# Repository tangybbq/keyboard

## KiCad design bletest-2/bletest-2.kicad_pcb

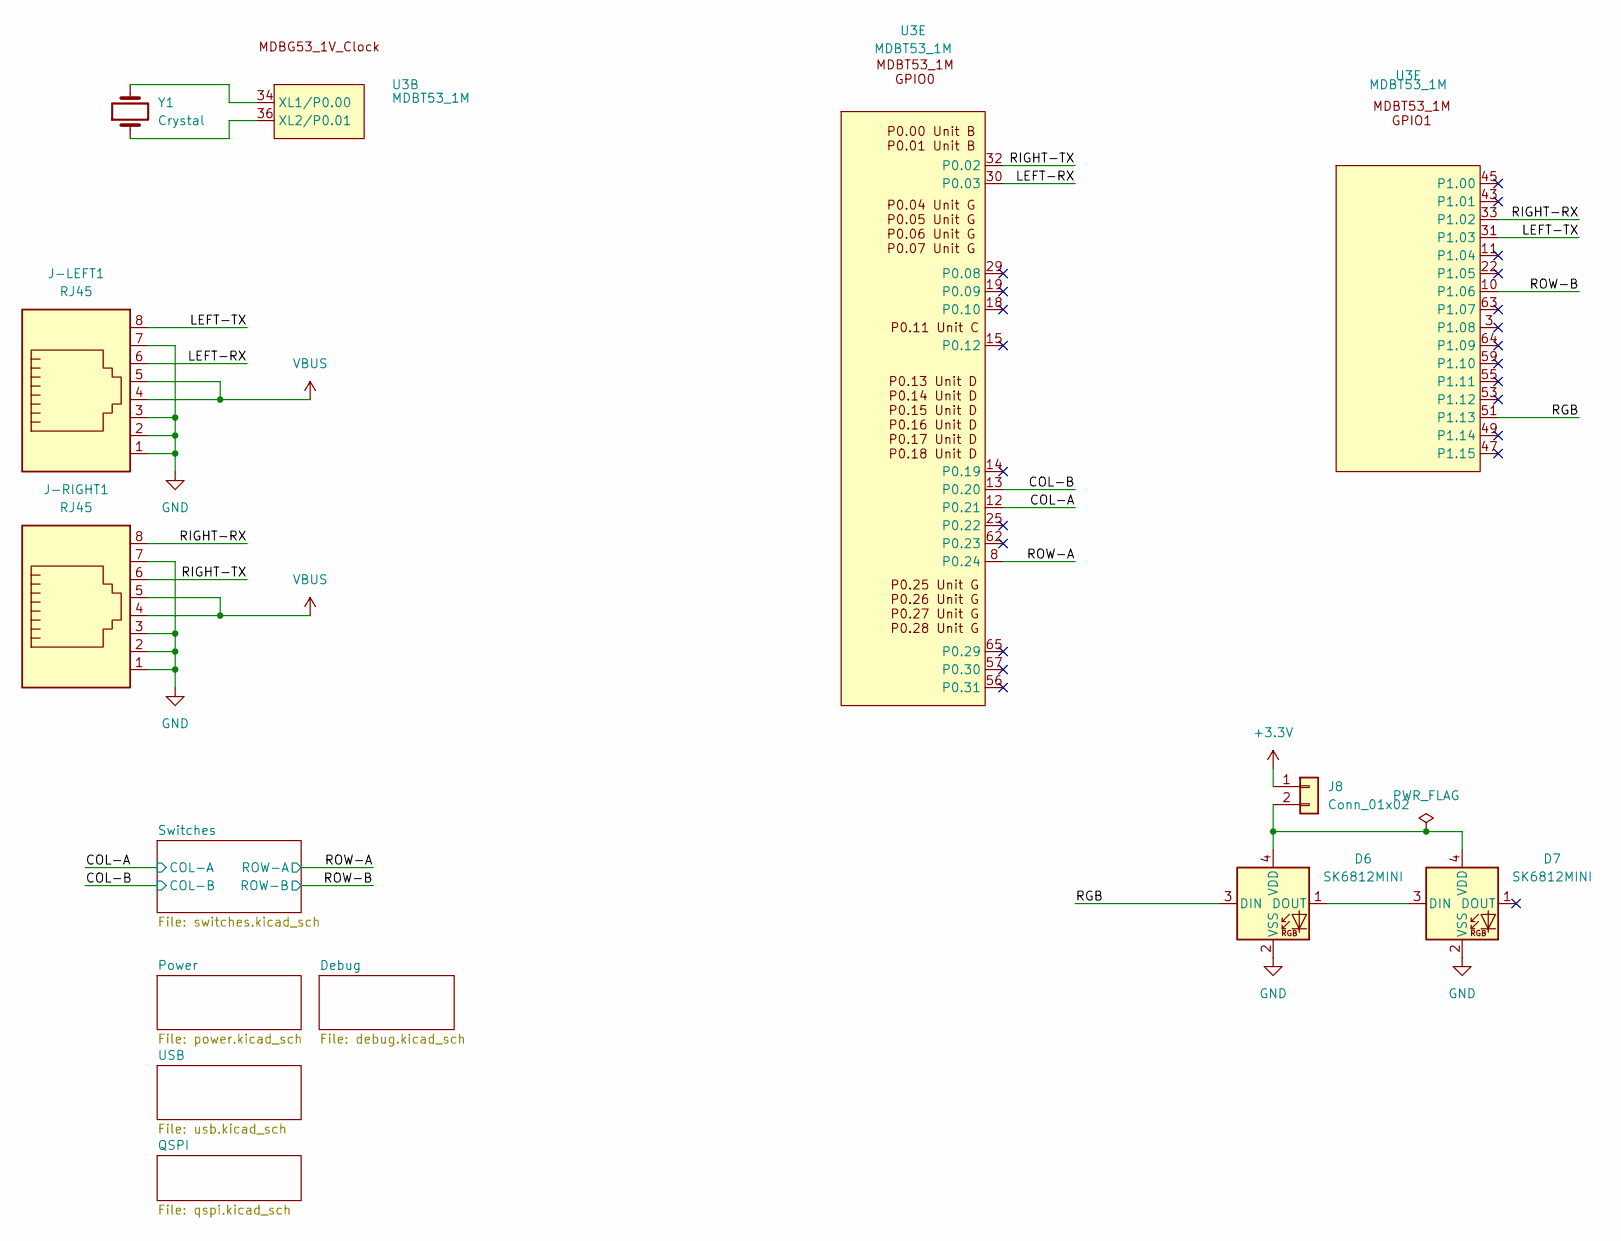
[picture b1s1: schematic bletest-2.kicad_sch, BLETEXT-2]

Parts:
D6, D7: SK6812MINI; LED_SK6812MINI_PLCC4_3.5x3.5mm_P1.75mm
J8: Conn_01x02; PinHeader_1x02_P2.54mm_Vertical
J-LEFT1: RJ45; RJ45_Amphenol_54602-x08_Horizontal
J-RIGHT1: RJ45; RJ45_Amphenol_54602-x08_Horizontal
U3: MDBT53_1M
Y1: Crystal; Crystal_SMD_3215-2Pin_3.2x1.5mm

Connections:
+3.3V: J8.1; also elsewhere on the board
/COL-A: U3.12 (P0.21); also elsewhere on the board
/COL-B: U3.13 (P0.20); also elsewhere on the board
/LEFT-RX: J-LEFT1.6, U3.30 (P0.03)
/LEFT-TX: J-LEFT1.8, U3.31 (P1.03)
/RGB: D6.3 (DIN), U3.51 (P1.13)
/RIGHT-RX: J-RIGHT1.8, U3.33 (P1.02)
/RIGHT-TX: J-RIGHT1.6, U3.32 (P0.02)
/ROW-A: U3.8 (P0.24); also elsewhere on the board
/ROW-B: U3.10 (P1.06); also elsewhere on the board
GND: D6.2 (VSS), D7.2 (VSS), J-LEFT1.1, J-LEFT1.2, J-LEFT1.3, J-LEFT1.7, J-RIGHT1.1, J-RIGHT1.2, J-RIGHT1.3, J-RIGHT1.7; also elsewhere on the board
unnamed: D6.1 (DOUT), D7.3 (DIN)
unnamed: D6.4 (VDD), D7.4 (VDD), J8.2
unnamed: U3.34 (XL1/P0.00), Y1.2
unnamed: U3.36 (XL2/P0.01), Y1.1
VBUS: J-LEFT1.4, J-LEFT1.5, J-RIGHT1.4, J-RIGHT1.5; also elsewhere on the board

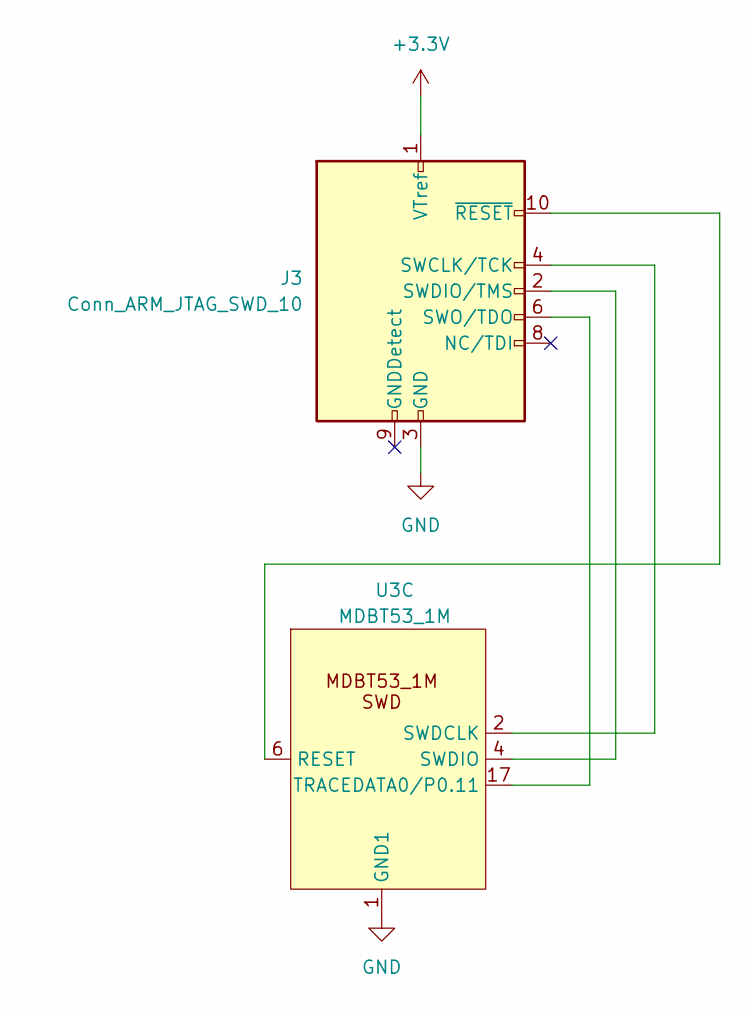
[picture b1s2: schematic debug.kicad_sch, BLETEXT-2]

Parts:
J3: Conn_ARM_JTAG_SWD_10; Cortex-M-Debug10
U3: MDBT53_1M

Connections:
+3.3V: J3.1 (VTref); also elsewhere on the board
GND: J3.3 (GND), J3.5 (GND), U3.1 (GND1); also elsewhere on the board
unnamed: J3.4 (SWCLK/TCK), U3.2 (SWDCLK)
unnamed: J3.2 (SWDIO/TMS), U3.4 (SWDIO)
unnamed: J3.6 (SWO/TDO), U3.17 (TRACEDATA0/P0.11)
unnamed: J3.10 (~RESET), U3.6 (RESET)

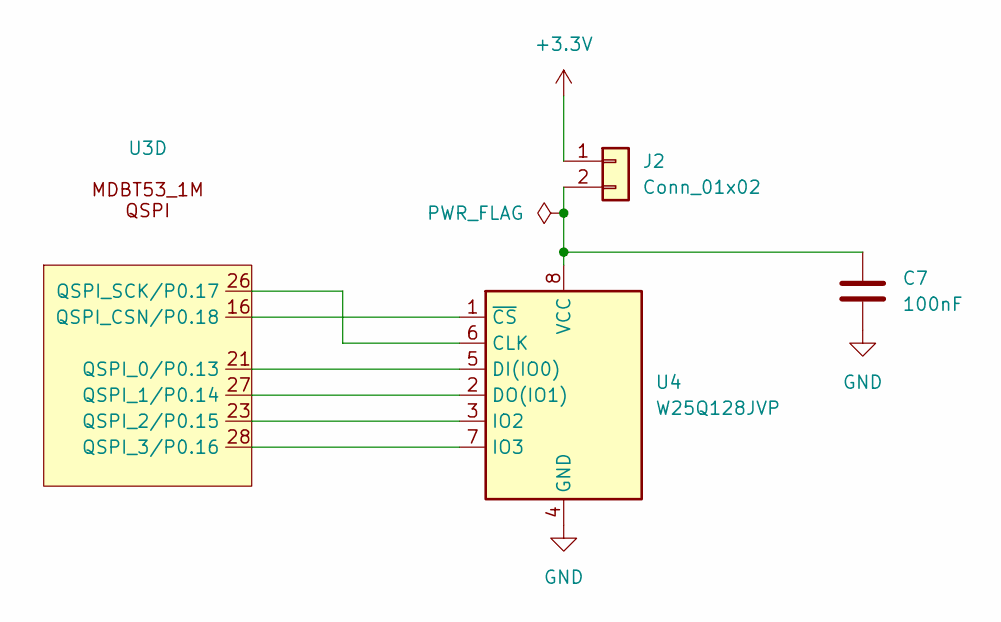
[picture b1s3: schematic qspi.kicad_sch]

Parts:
C7: 100nF; C_0603_1608Metric
J2: Conn_01x02; PinHeader_1x02_P2.54mm_Vertical
U3: MDBT53_1M
U4: W25Q128JVP; WSON-8-1EP_6x5mm_P1.27mm_EP3.4x4.3mm

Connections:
+3.3V: J2.1; also elsewhere on the board
GND: C7.2, U4.4 (GND); also elsewhere on the board
unnamed: C7.1, J2.2, U4.8 (VCC)
unnamed: U3.21 (QSPI_0/P0.13), U4.5 (DI(IO0))
unnamed: U3.27 (QSPI_1/P0.14), U4.2 (DO(IO1))
unnamed: U3.23 (QSPI_2/P0.15), U4.3 (IO2)
unnamed: U3.28 (QSPI_3/P0.16), U4.7 (IO3)
unnamed: U3.16 (QSPI_CSN/P0.18), U4.1 (~CS)
unnamed: U3.26 (QSPI_SCK/P0.17), U4.6 (CLK)

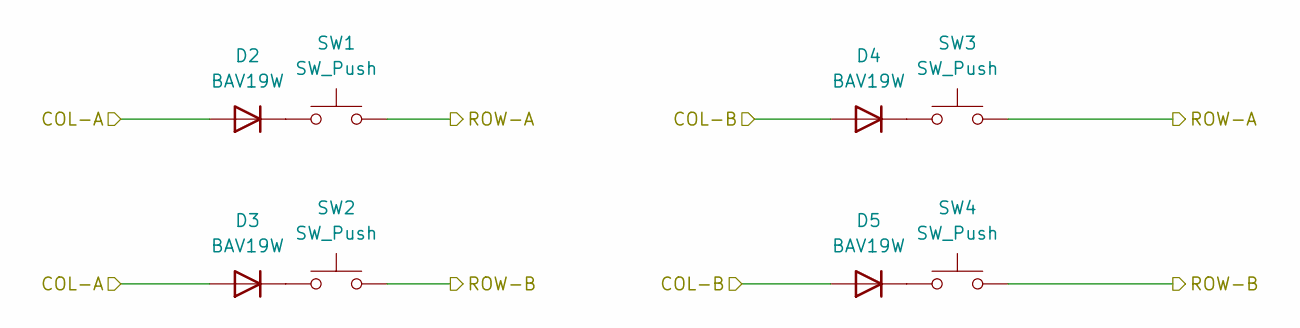
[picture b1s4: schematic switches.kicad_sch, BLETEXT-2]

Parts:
D2, D3, D4, D5: BAV19W; Nexperia_CFP3_SOD-123W
SW1, SW2, SW3, SW4: SW_Push; Kailh_socket_PG1350

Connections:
/COL-A: D2.2 (A), D3.2 (A); also elsewhere on the board
/COL-B: D4.2 (A), D5.2 (A); also elsewhere on the board
/ROW-A: SW1.2, SW3.2; also elsewhere on the board
/ROW-B: SW2.2, SW4.2; also elsewhere on the board
unnamed: D2.1 (K), SW1.1
unnamed: D3.1 (K), SW2.1
unnamed: D4.1 (K), SW3.1
unnamed: D5.1 (K), SW4.1

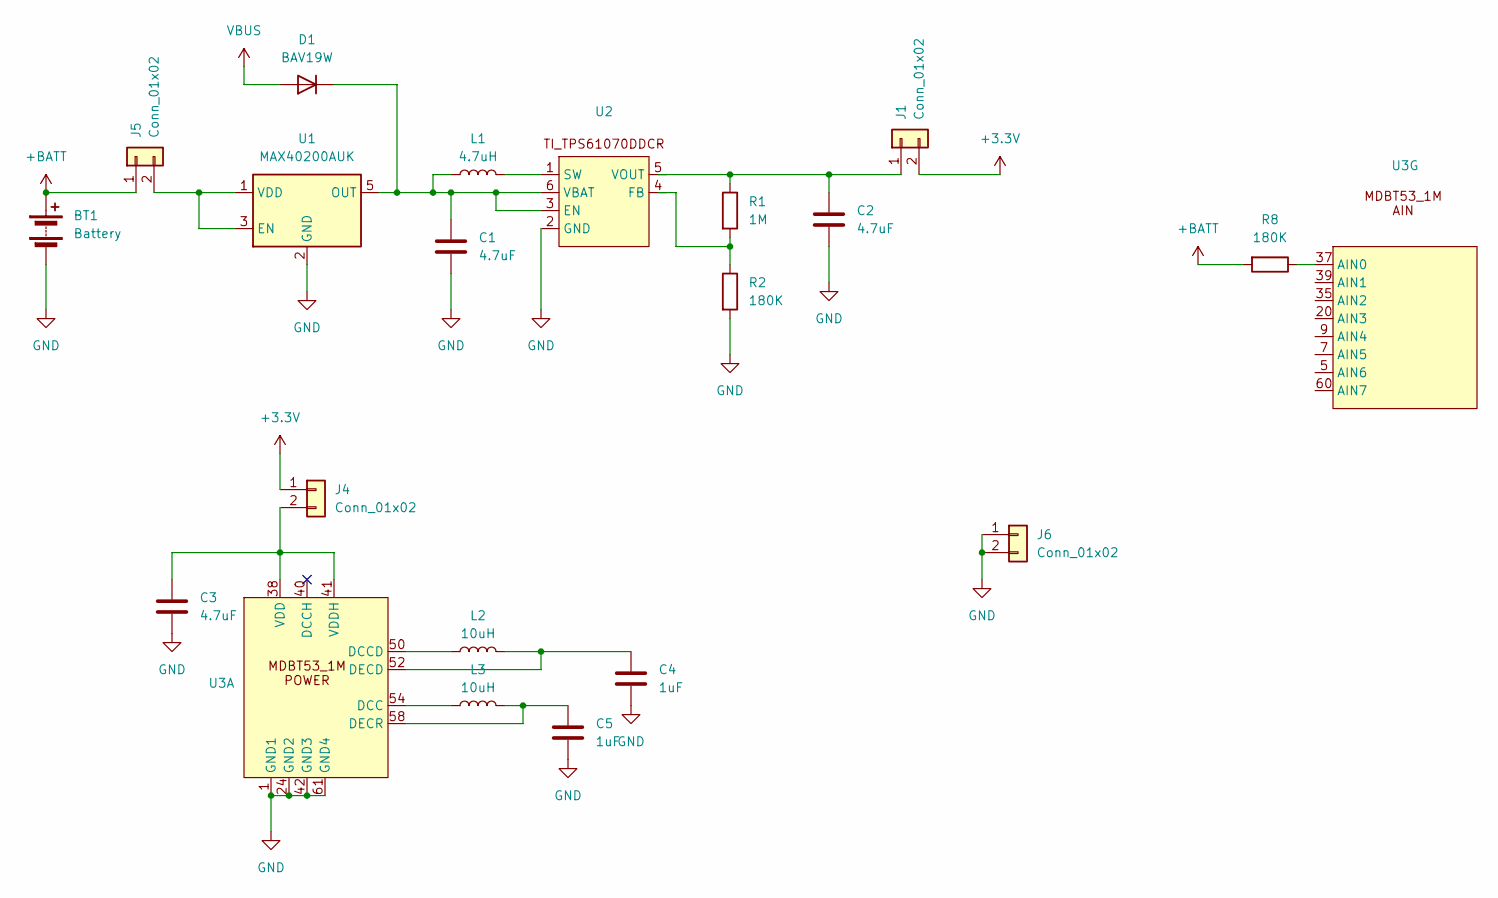
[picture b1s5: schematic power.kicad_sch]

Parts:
BT1: Battery; BAT-2xAA-SHELL-CASE-BOX-NOSCREW
C1, C2, C3: 4.7uF; C_0603_1608Metric
C4, C5: 1uF; C_0603_1608Metric
D1: BAV19W; Nexperia_CFP3_SOD-123W
J1, J4, J5, J6: Conn_01x02; PinHeader_1x02_P2.54mm_Vertical
L1: 4.7uH; L_0805_2012Metric
L2, L3: 10uH; L_0805_2012Metric
R1: 1M; R_0603_1608Metric
R2, R8: 180K; R_0603_1608Metric
U1: MAX40200AUK; SOT-23-5
U2: SOT-23-6
U3: MDBT53_1M

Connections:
+3.3V: J1.2, J4.1; also elsewhere on the board
+BATT: BT1.1 (+), J5.1, R8.2
GND: BT1.2 (-), C1.2, C2.2, C3.2, C4.2, C5.2, J6.1, J6.2, R2.2, U1.2 (GND), U2.2 (GND), U3.1 (GND1), U3.24 (GND2), U3.42 (GND3), U3.61 (GND4); also elsewhere on the board
unnamed: C1.1, D1.1 (K), L1.1, U1.5 (OUT), U2.3 (EN), U2.6 (VBAT)
unnamed: C3.1, J4.2, U3.38 (VDD), U3.41 (VDDH)
unnamed: J5.2, U1.1 (VDD), U1.3 (EN)
unnamed: L1.2, U2.1 (SW)
unnamed: L3.1, U3.54 (DCC)
unnamed: L2.1, U3.50 (DCCD)
unnamed: C4.1, L2.2, U3.52 (DECD)
unnamed: C5.1, L3.2, U3.58 (DECR)
unnamed: R8.1, U3.37 (AIN0/P0.04)
VBUS: D1.2 (A); also elsewhere on the board

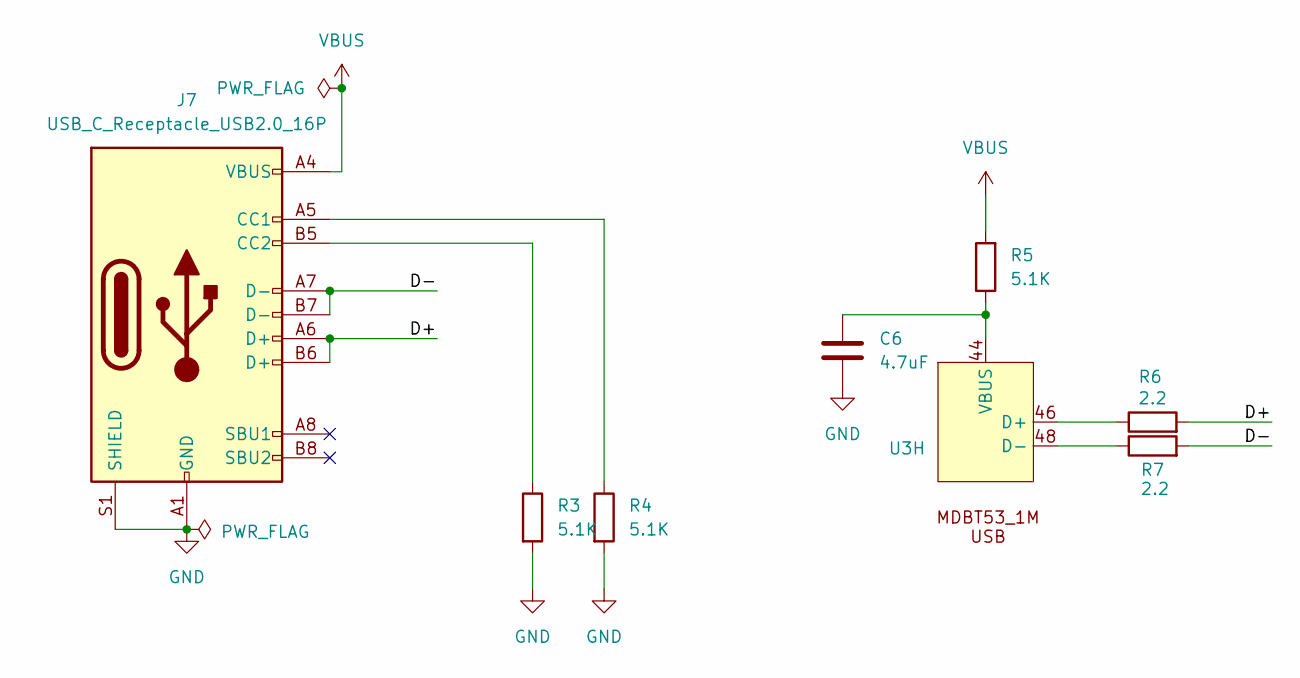
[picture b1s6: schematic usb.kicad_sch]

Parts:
C6: 4.7uF; C_0603_1608Metric
J7: USB_C_Receptacle_USB2.0_16P; USB_C_Receptacle_GCT_USB4085
R3, R4, R5: 5.1K; R_0603_1608Metric
R6, R7: 2.2; R_0603_1608Metric
U3: MDBT53_1M

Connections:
/USB/D+: J7.A6 (D+), J7.B6 (D+), R6.2
/USB/D-: J7.A7 (D-), J7.B7 (D-), R7.2
GND: C6.2, J7.A1 (GND), J7.A12 (GND), J7.B1 (GND), J7.B12 (GND), J7.S1 (SHIELD), R3.2, R4.2; also elsewhere on the board
unnamed: J7.A5 (CC1), R4.1
unnamed: J7.B5 (CC2), R3.1
unnamed: R6.1, U3.46 (D+)
unnamed: R7.1, U3.48 (D-)
unnamed: C6.1, R5.1, U3.44 (VBUS)
VBUS: J7.A4 (VBUS), J7.A9 (VBUS), J7.B4 (VBUS), J7.B9 (VBUS), R5.2; also elsewhere on the board

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
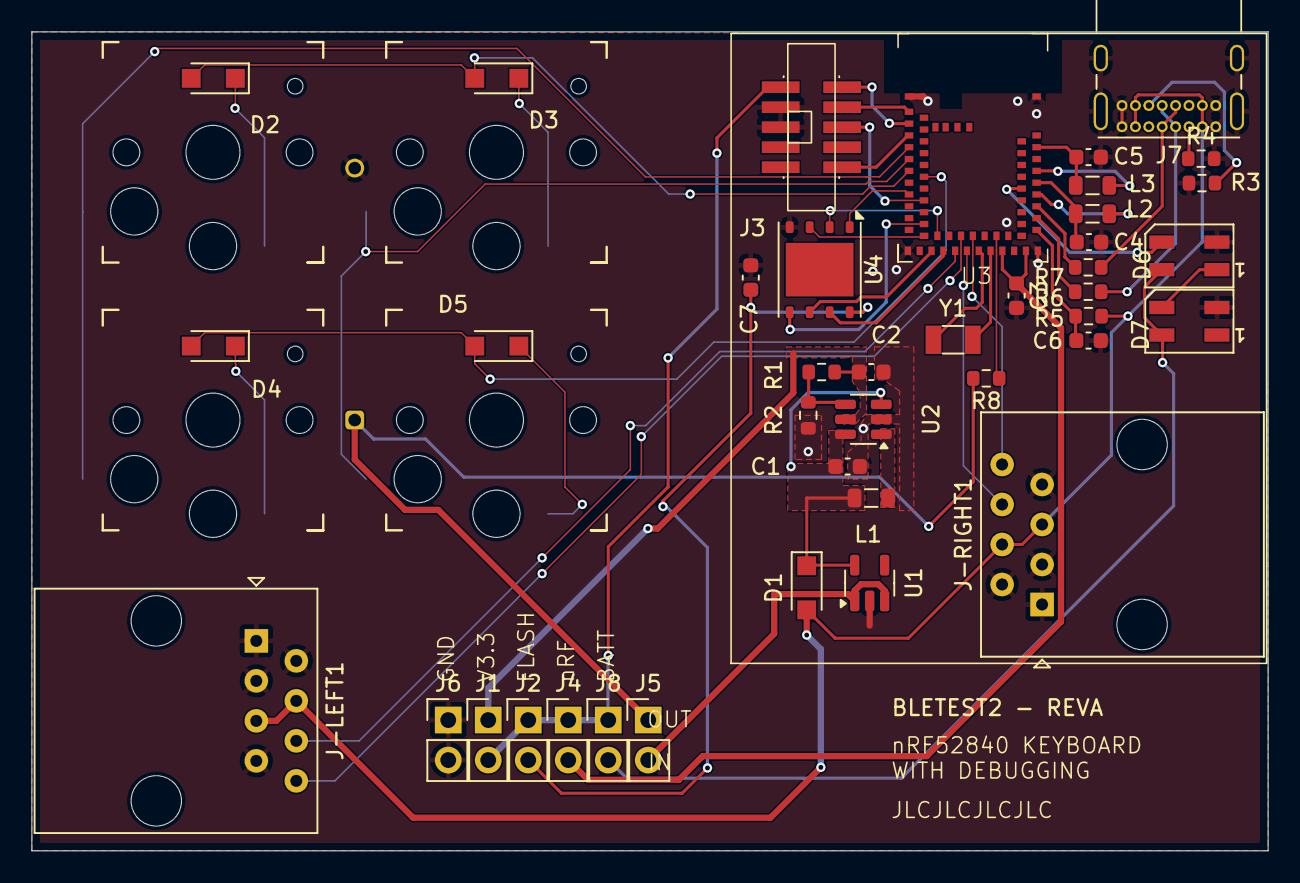
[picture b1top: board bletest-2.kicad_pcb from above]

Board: 2 copper layers, 78.5 x 52.0 mm, 45 parts (1 on the bottom side), 50 nets.

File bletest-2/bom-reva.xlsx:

Reference | Value | Qty | Datasheet | Footprint | DNP
BT1 | Battery | 1 | ~ | davidb-keyboard-foot:BAT-2xAA-SHELL-CASE-BOX-NOSCREW
C1,C2,C3,C6 | 4.7uF | 4 | ~ | Capacitor_SMD:C_0603_1608Metric
C4,C5 | 1uF | 2 | ~ | Capacitor_SMD:C_0603_1608Metric
C7 | 100nF | 1 | ~ | Capacitor_SMD:C_0603_1608Metric
D1,D2,D3,D4,D5 | BAV19W | 5 | ~ | Diode_SMD:Nexperia_CFP3_SOD-123W
D6,D7 | SK6812MINI | 2 | https://cdn-shop.adafruit.com/product-files/2686/SK6812MINI_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 | LED_SMD:LED_SK6812MINI_PLCC4_3.5x3.5mm_P1.75mm
J-LEFT1,J-RIGHT1 | RJ45 | 2 | ~ | Connector_RJ:RJ45_Amphenol_54602-x08_Horizontal
J1,J2,J4,J5,J6,J8 | Conn_01x02 | 6 | ~ | Connector_PinHeader_2.54mm:PinHeader_1x02_P2.54mm_Vertical
J3 | Conn_ARM_JTAG_SWD_10 | 1 | http://infocenter.arm.com/help/topic/com.arm.doc.ddi0314h/DD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 | davidb-keyboard-foot:Cortex-M-Debug10
J7 | USB_C_Receptacle_USB2.0_16P | 1 | https://www.usb.org/sites/default/files/documents/usb_type-c.zip | Connector_USB:USB_C_Receptacle_GCT_USB4085
L1 | 4.7uH | 1 | ~ | Inductor_SMD:L_0805_2012Metric
L2,L3 | 10uH | 2 | ~ | Inductor_SMD:L_0805_2012Metric
R1 | 1M | 1 | ~ | Resistor_SMD:R_0603_1608Metric
R2,R8 | 180K | 2 | ~ | Resistor_SMD:R_0603_1608Metric
R3,R4,R5 | 5.1K | 3 | ~ | Resistor_SMD:R_0603_1608Metric
R6,R7 | 2.2000000000000002 | 2 | ~ | Resistor_SMD:R_0603_1608Metric
SW1,SW2,SW3,SW4 | SW_Push | 4 | ~ | Keyboard Switches:Kailh_socket_PG1350
U1 | MAX40200AUK | 1 | https://datasheets.maximintegrated.com/en/ds/MAX40200.pdf | Package_TO_SOT_SMD:SOT-23-5
U2,U3 | ~ | 2 |  | -- mixed values --
U4 | W25Q128JVP | 1 | https://www.winbond.com/resource-files/w25q128jv_dtr%20revc%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 | Package_SON:WSON-8-1EP_6x5mm_P1.27mm_EP3.4x4.3mm
Y1 | Crystal | 1 | ~ | Crystal:Crystal_SMD_3215-2Pin_3.2x1.5mm

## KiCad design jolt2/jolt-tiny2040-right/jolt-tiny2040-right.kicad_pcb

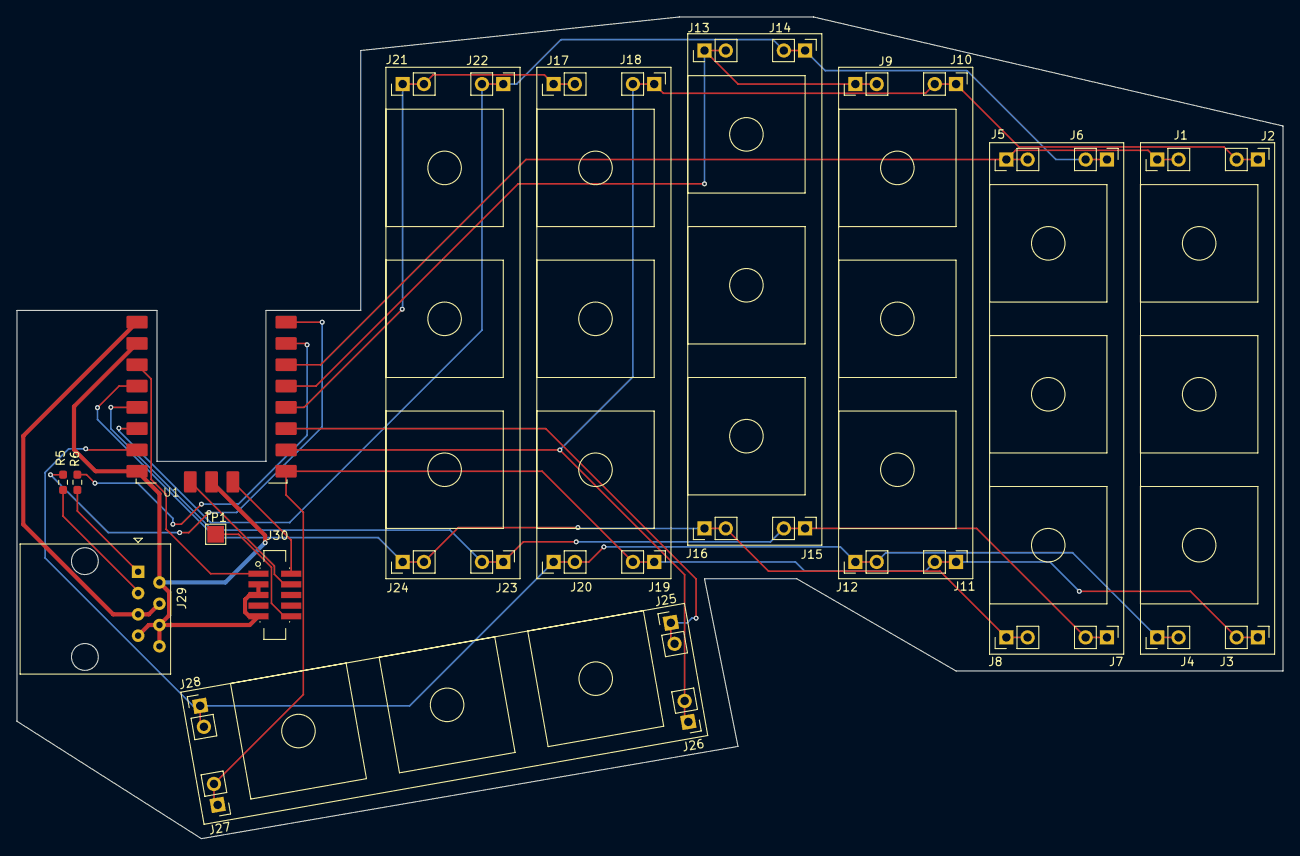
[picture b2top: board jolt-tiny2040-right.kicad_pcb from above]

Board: 2 copper layers, 151.0 x 98.0 mm, 34 parts (0 on the bottom side), 20 nets.

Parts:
J1, J2, J3, J4, J5, J6, J7, J8, J9, J10, J11, J12, J13, J14, J15, J16, J17, J18, J19, J20, J21, J22, J23, J24, J25, J26, J27, J28: Conn_01x02_Pin; PinHeader_1x02_P2.54mm_Vertical
J29: RJ45; RJ45_Amphenol_54602-x08_Horizontal
J30: Conn_ARM_JTAG_SWD_10; Cortex-M-Debug10
R5, R6: 27; R_0603_1608Metric_Pad0.98x0.95mm_HandSolder
TP1: Reset; TestPoint_Pad_2.0x2.0mm
U1: Pimoroni-Tiny2040

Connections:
+3.3V: J30.1 (VTref), U1.3V
/COL-A: J1.1, J1.2, J5.1, J5.2, U1.2
/COL-B: J9.1, J9.2, J13.1, J13.2, U1.3
/COL-C: J17.1, J17.2, J21.1, J21.2, U1.4
/COL-D: J25.1, J25.2, U1.5
/ROW-A: J2.1, J2.2, J10.1, J10.2, J18.1, J18.2, J26.1, J26.2, U1.6
/ROW-B: J3.1, J3.2, J11.1, J11.2, J19.1, J19.2, J27.1, J27.2, U1.7
/ROW-C: J4.1, J4.2, J12.1, J12.2, J20.1, J20.2, J28.1, J28.2, U1.A0
/ROW-D: J6.1, J6.2, J14.1, J14.2, J22.1, J22.2, U1.A1
/ROW-E: J7.1, J7.2, J15.1, J15.2, J23.1, J23.2, U1.A2
/ROW-F: J8.1, J8.2, J16.1, J16.2, J24.1, J24.2, U1.A3
GND: J29.2, J29.6, J29.7, J29.8, J30.3 (GND), J30.5 (GND), J30.9 (GNDDetect), U1.GND1 (GND), U1.GND2 (GND), U1.GND3 (GND)
unnamed: R5.1, U1.0
unnamed: R6.1, U1.1
RUN: J30.10 (~RESET), TP1.1
SERRX: J29.1, R6.2
SERTX: J29.3, R5.2
SWCLK: J30.4 (SWCLK/TCK), U1.SWC
SWDIO: J30.2 (SWDIO/TMS), U1.SWD
VBUS: J29.4, J29.5, U1.5V

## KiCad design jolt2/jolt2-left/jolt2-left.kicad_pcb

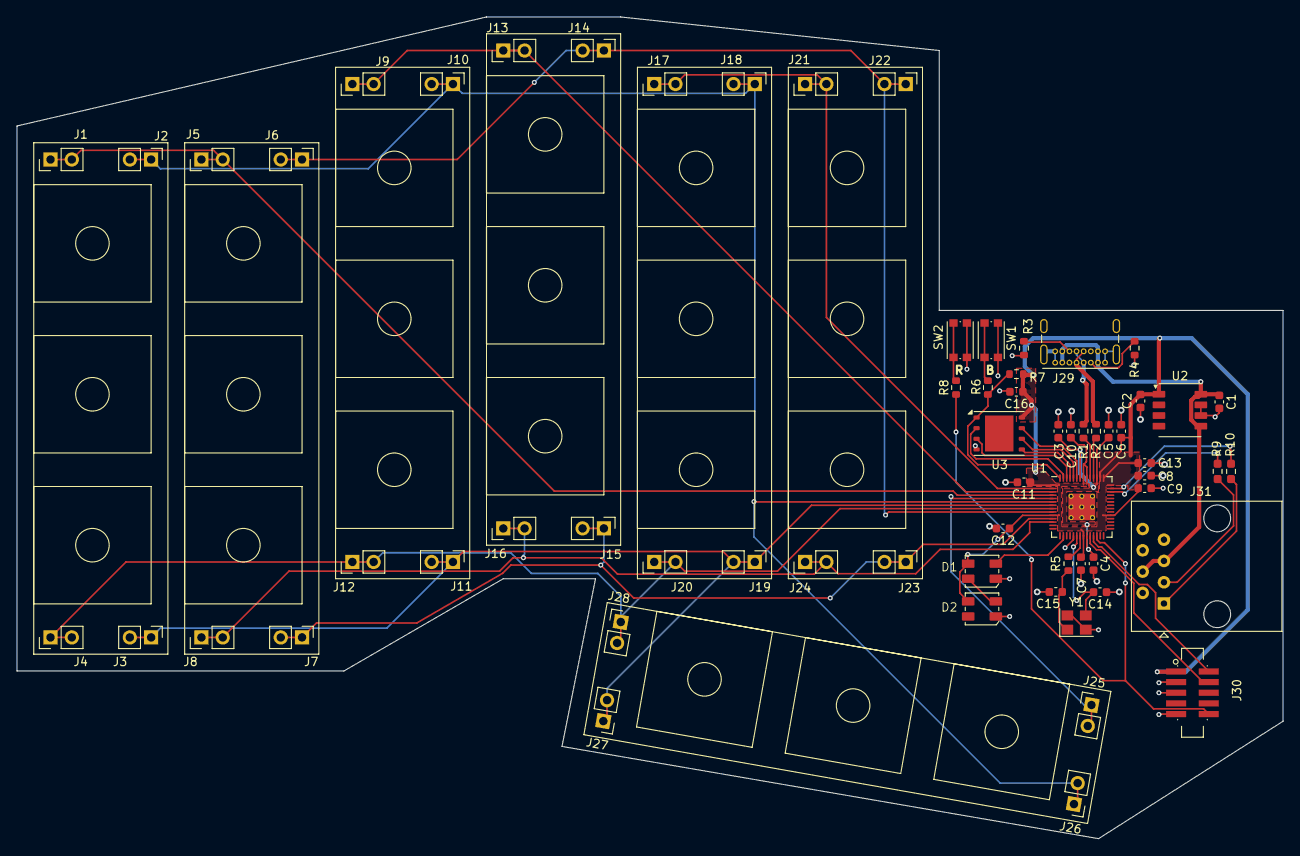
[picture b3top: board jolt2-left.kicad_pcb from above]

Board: 2 copper layers, 151.0 x 98.0 mm, 65 parts (0 on the bottom side), 40 nets.

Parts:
C1, C2: 10u; C_0603_1608Metric
C3, C4, C7, C8, C9, C10, C11, C12, C13, C16: 100n; C_0603_1608Metric
C5, C6: 1u; C_0603_1608Metric
C14, C15: 12p; C_0603_1608Metric
D1, D2: SK6812MINI-HS; SK6812-MINI-HS
J1, J2, J3, J4, J5, J6, J7, J8, J9, J10, J11, J12, J13, J14, J15, J16, J17, J18, J19, J20, J21, J22, J23, J24, J25, J26, J27, J28: Conn_01x02_Pin; PinHeader_1x02_P2.54mm_Vertical
J29: USB_C_Receptacle_USB2.0_14P; USB_C_Receptacle_GCT_USB4085
J30: Conn_ARM_JTAG_SWD_10; Cortex-M-Debug10
J31: RJ45; RJ45_Amphenol_54602-x08_Horizontal
R1, R2: 27; R_0603_1608Metric
R3, R4: 5.1k; R_0603_1608Metric
R5, R6, R8: 1k; R_0603_1608Metric
R7: 10k; R_0603_1608Metric
R9, R10: 27; R_0603_1608Metric_Pad0.98x0.95mm_HandSolder
SW1, SW2: SW_SPST; SW_Push_1P1T_NO_CK_KMR2
U1: RP2040; RP2040-QFN-56
U2: AP2112-M3.3; AP2112M-SO8
U3: W25Q128JVP; WSON-8-1EP_6x5mm_P1.27mm_EP3.4x4.3mm
Y1: ABM8-272-T3; Crystal_SMD_Abracon_ABM8G-4Pin_3.2x2.5mm

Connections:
+1V1: C3.1, C4.1, C5.1, U1.23 (DVDD), U1.45 (VREG_VOUT), U1.50 (DVDD)
+3.3V: C2.1, C6.1, C7.1, C8.1, C9.1, C10.1, C11.1, C12.1, C13.1, C16.1, D1.3 (VDD), D2.3 (VDD), J30.1 (VTref), R7.2, U1.1 (IOVDD), U1.10 (IOVDD), U1.22 (IOVDD), U1.33 (IOVDD), U1.42 (IOVDD), U1.43 (ADC_AVDD), U1.44 (VREG_IN), U1.48 (USB_VDD), U1.49 (IOVDD), U2.1 (VOUT), U3.8 (VCC)
/COL-A: J1.1, J1.2, J5.1, J5.2, U1.4 (GPIO2)
/COL-B: J9.1, J9.2, J13.1, J13.2, U1.3 (GPIO1)
/COL-C: J17.1, J17.2, J21.1, J21.2, U1.2 (GPIO0)
/COL-D: J25.1, J25.2, U1.5 (GPIO3)
/ROW-A: J2.1, J2.2, J10.1, J10.2, J18.1, J18.2, J26.1, J26.2, U1.6 (GPIO4)
/ROW-B: J3.1, J3.2, J11.1, J11.2, J19.1, J19.2, J27.1, J27.2, U1.7 (GPIO5)
/ROW-C: J4.1, J4.2, J12.1, J12.2, J20.1, J20.2, J28.1, J28.2, U1.8 (GPIO6)
/ROW-D: J6.1, J6.2, J14.1, J14.2, J22.1, J22.2, U1.9 (GPIO7)
/ROW-E: J7.1, J7.2, J15.1, J15.2, J23.1, J23.2, U1.11 (GPIO8)
/ROW-F: J8.1, J8.2, J16.1, J16.2, J24.1, J24.2, U1.12 (GPIO9)
/USB_D+: J29.A6 (D+), J29.B6 (D+), R1.2
/USB_D-: J29.A7 (D-), J29.B7 (D-), R2.2
GND: C1.2, C2.2, C3.2, C4.2, C5.2, C6.2, C7.2, C8.2, C9.2, C10.2, C11.2, C12.2, C13.2, C14.1, C15.1, C16.2, D1.1 (VSS), D2.1 (VSS), J29.A1 (GND), J29.A12 (GND), J29.B1 (GND), J29.B12 (GND), J29.S1 (SHIELD), J30.3 (GND), J30.5 (GND), J30.9 (GNDDetect), J31.2, J31.6, J31.7, J31.8, R3.2, R4.2, SW1.1 (A), SW2.1 (A), U1.19 (TESTEN), U1.57 (GND), U2.6 (GND), U2.7 (GND), U3.4 (GND), Y1.2, Y1.4
unnamed: C15.2, R5.1, Y1.1
unnamed: D1.4 (DOUT), D2.2 (DIN)
unnamed: J29.A5 (CC1), R4.1
unnamed: J29.B5 (CC2), R3.1
unnamed: J31.1, R10.1
unnamed: J31.3, R9.1
unnamed: R6.1, SW1.2 (B)
unnamed: R8.2, SW2.2 (B)
unnamed: R2.1, U1.46 (USB_DM)
unnamed: R1.1, U1.47 (USB_DP)
unnamed: C14.2, U1.20 (XIN), Y1.3
unnamed: R5.2, U1.21 (XOUT)
QSPI.SCLK: U1.52 (QSPI_SCLK), U3.6 (CLK)
QSPI.SD0: U1.53 (QSPI_SD0), U3.5 (DI(IO0))
QSPI.SD1: U1.55 (QSPI_SD1), U3.2 (DO(IO1))
QSPI.SD2: U1.54 (QSPI_SD2), U3.3 (IO2)
QSPI.SD3: U1.51 (QSPI_SD3), U3.7 (IO3)
QSPI.SS: R6.2, R7.1, U1.56 (QSPI_SS), U3.1 (~CS)
RGB: D1.2 (DIN), U1.16 (GPIO13)
RUN: J30.10 (~RESET), R8.1, U1.26 (RUN)
SERRX: R10.2, U1.41 (GPIO29_ADC3)
SERTX: R9.2, U1.40 (GPIO28_ADC2)
SWCLK: J30.4 (SWCLK/TCK), U1.24 (SWCLK)
SWDIO: J30.2 (SWDIO/TMS), U1.25 (SWD)
VBUS: C1.1, J29.A4 (VBUS), J29.A9 (VBUS), J29.B4 (VBUS), J29.B9 (VBUS), J31.4, J31.5, U2.5 (EN), U2.8 (VIN)

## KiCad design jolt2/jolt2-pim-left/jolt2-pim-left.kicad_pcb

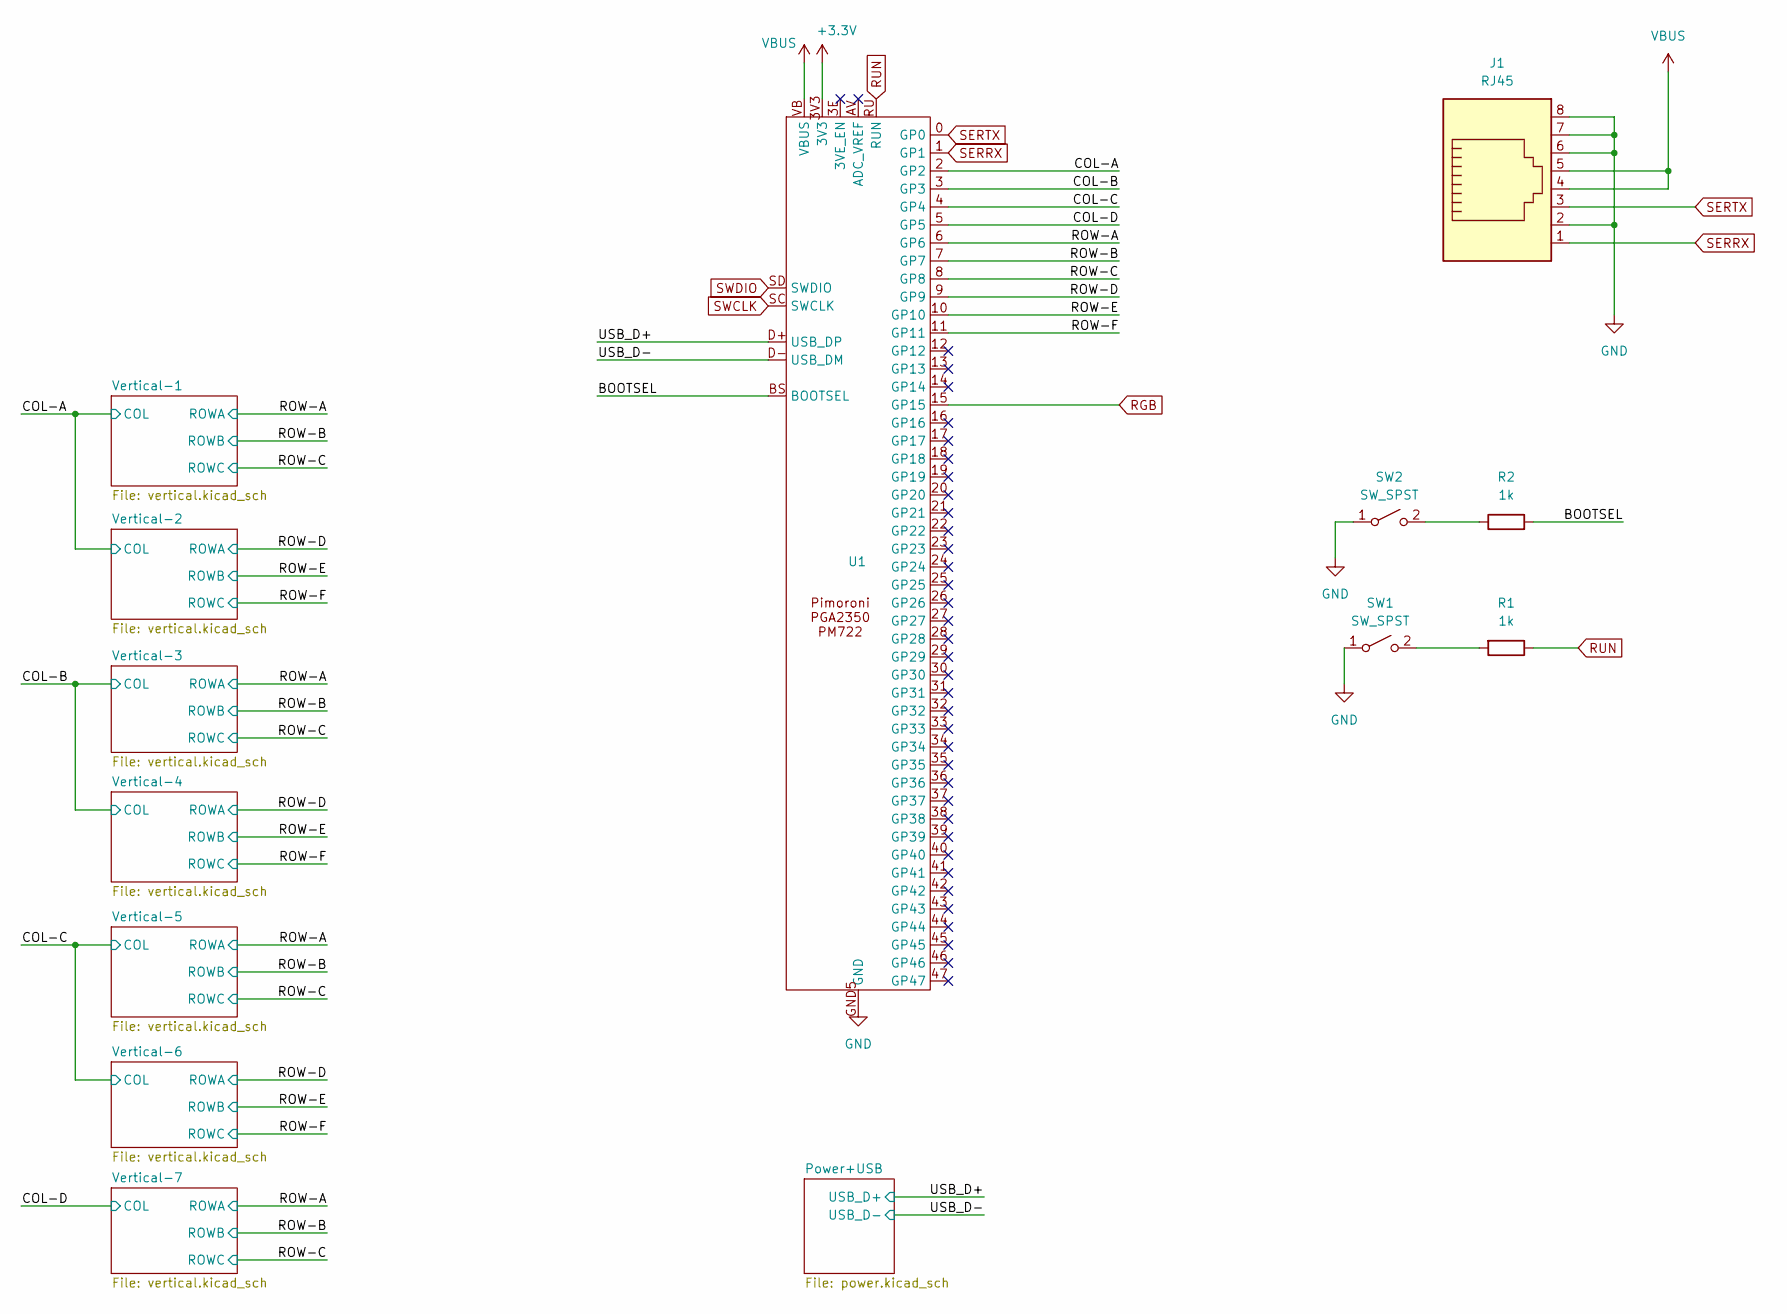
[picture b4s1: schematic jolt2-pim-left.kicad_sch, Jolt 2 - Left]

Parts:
J1: RJ45; RJ45_Amphenol_54602-x08_Horizontal
R1, R2: 1k; R_0603_1608Metric
SW1, SW2: SW_SPST; SW_Push_1P1T_NO_CK_KMR2
U1: PIMORONI-PGA2035-PM722

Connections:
+3.3V: U1.3V3; also elsewhere on the board
/BOOTSEL: R2.2, U1.BS (BOOTSEL)
/COL-A: U1.2 (GP2); also elsewhere on the board
/COL-B: U1.3 (GP3); also elsewhere on the board
/COL-C: U1.4 (GP4); also elsewhere on the board
/COL-D: U1.5 (GP5); also elsewhere on the board
/ROW-A: U1.6 (GP6); also elsewhere on the board
/ROW-B: U1.7 (GP7); also elsewhere on the board
/ROW-C: U1.8 (GP8); also elsewhere on the board
/ROW-D: U1.9 (GP9); also elsewhere on the board
/ROW-E: U1.10 (GP10); also elsewhere on the board
/ROW-F: U1.11 (GP11); also elsewhere on the board
/USB_D+: U1.D+ (USB_DP); also elsewhere on the board
/USB_D-: U1.D- (USB_DM); also elsewhere on the board
GND: J1.2, J1.6, J1.7, J1.8, SW1.1 (A), SW2.1 (A), U1.GND1 (GND), U1.GND2 (GND), U1.GND3 (GND), U1.GND4 (GND), U1.GND5 (GND), U1.GND6 (GND); also elsewhere on the board
unnamed: R1.2, SW1.2 (B)
unnamed: R2.1, SW2.2 (B)
RGB: U1.15 (GP15); also elsewhere on the board
RUN: R1.1, U1.RU (RUN); also elsewhere on the board
SERRX: J1.1, U1.1 (GP1)
SERTX: J1.3, U1.0 (GP0)
SWCLK: U1.SC (SWCLK); also elsewhere on the board
SWDIO: U1.SD (SWDIO); also elsewhere on the board
VBUS: J1.4, J1.5, U1.VB (VBUS); also elsewhere on the board

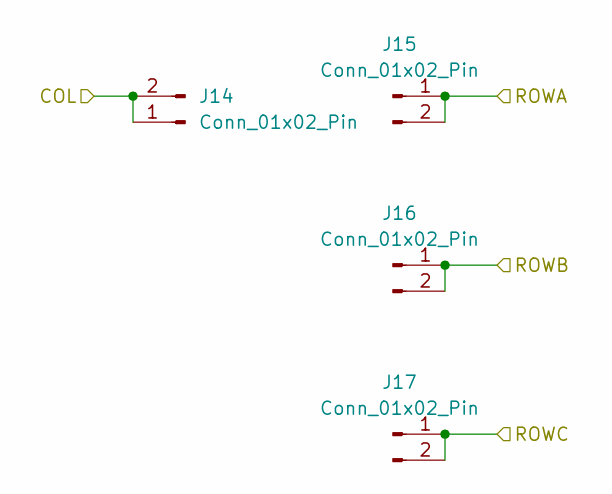
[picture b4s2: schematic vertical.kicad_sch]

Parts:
J14, J15, J16, J17: Conn_01x02_Pin; PinHeader_1x02_P2.54mm_Vertical

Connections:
/COL-B: J14.1, J14.2; also elsewhere on the board
/ROW-D: J15.1, J15.2; also elsewhere on the board
/ROW-E: J16.1, J16.2; also elsewhere on the board
/ROW-F: J17.1, J17.2; also elsewhere on the board

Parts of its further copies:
J2, J3, J4, J5, J6, J7, J8, J9, J10, J11, J12, J13, J18, J19, J20, J21, J22, J23, J24, J25, J26, J27, J28, J29: Conn_01x02_Pin; PinHeader_1x02_P2.54mm_Vertical

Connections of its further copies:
/COL-A: J2.1, J2.2, J6.1, J6.2; also elsewhere on the board
/COL-B: J10.1, J10.2; also elsewhere on the board
/COL-C: J18.1, J18.2, J22.1, J22.2; also elsewhere on the board
/COL-D: J26.1, J26.2; also elsewhere on the board
/ROW-A: J3.1, J3.2, J11.1, J11.2, J19.1, J19.2, J27.1, J27.2; also elsewhere on the board
/ROW-B: J4.1, J4.2, J12.1, J12.2, J20.1, J20.2, J28.1, J28.2; also elsewhere on the board
/ROW-C: J5.1, J5.2, J13.1, J13.2, J21.1, J21.2, J29.1, J29.2; also elsewhere on the board
/ROW-D: J7.1, J7.2, J23.1, J23.2; also elsewhere on the board
/ROW-E: J8.1, J8.2, J24.1, J24.2; also elsewhere on the board
/ROW-F: J9.1, J9.2, J25.1, J25.2; also elsewhere on the board

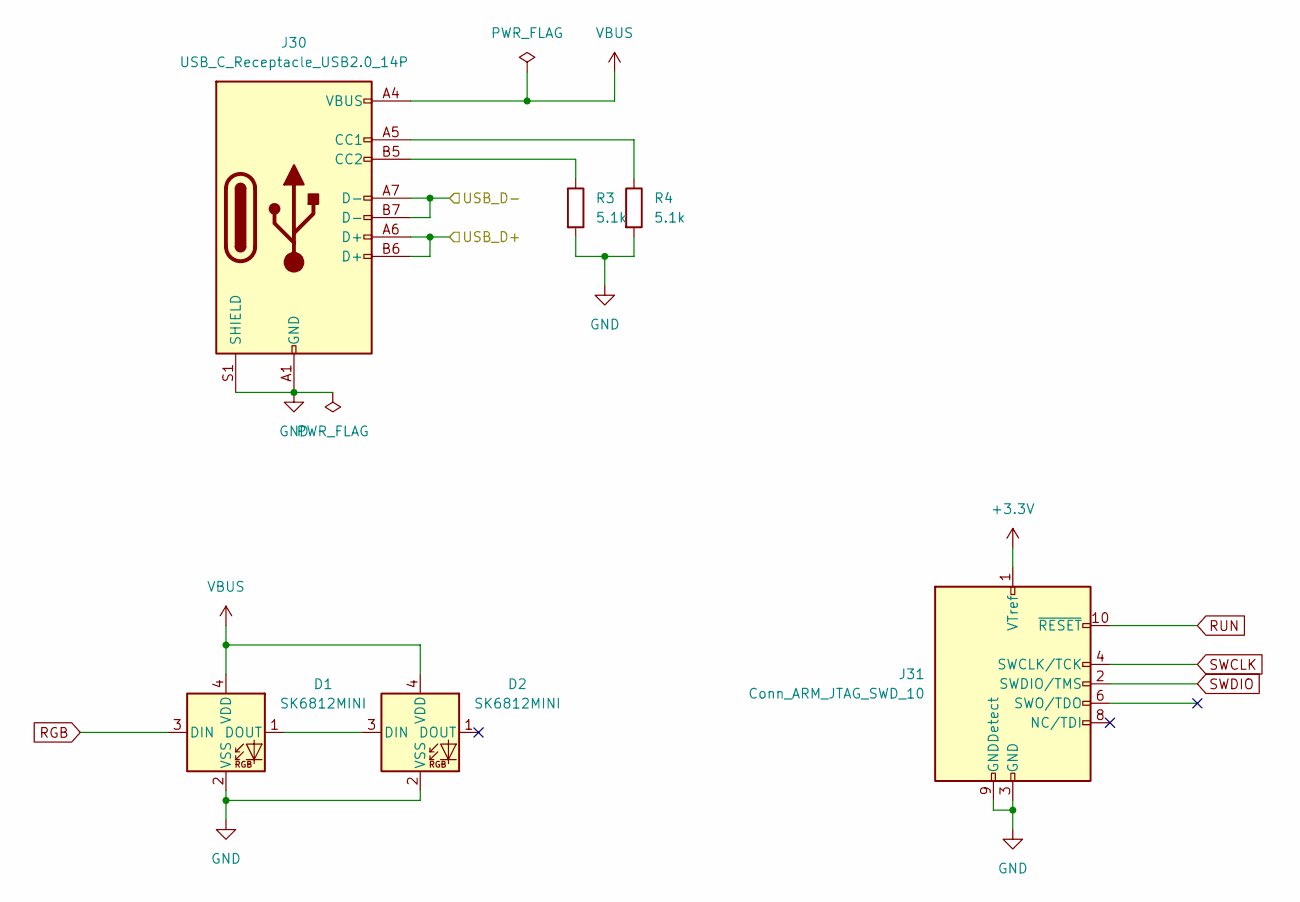
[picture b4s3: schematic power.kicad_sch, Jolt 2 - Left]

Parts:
D1, D2: SK6812MINI; LED_SK6812MINI_PLCC4_3.5x3.5mm_P1.75mm
J30: USB_C_Receptacle_USB2.0_14P; USB_C_Receptacle_GCT_USB4085
J31: Conn_ARM_JTAG_SWD_10; Cortex-M-Debug10
R3, R4: 5.1k; R_0603_1608Metric

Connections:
+3.3V: J31.1 (VTref); also elsewhere on the board
/USB_D+: J30.A6 (D+), J30.B6 (D+); also elsewhere on the board
/USB_D-: J30.A7 (D-), J30.B7 (D-); also elsewhere on the board
GND: D1.2 (VSS), D2.2 (VSS), J30.A1 (GND), J30.A12 (GND), J30.B1 (GND), J30.B12 (GND), J30.S1 (SHIELD), J31.3 (GND), J31.5 (GND), J31.9 (GNDDetect), R3.2, R4.2; also elsewhere on the board
unnamed: D1.1 (DOUT), D2.3 (DIN)
unnamed: J30.A5 (CC1), R4.1
unnamed: J30.B5 (CC2), R3.1
RGB: D1.3 (DIN); also elsewhere on the board
RUN: J31.10 (~RESET); also elsewhere on the board
SWCLK: J31.4 (SWCLK/TCK); also elsewhere on the board
SWDIO: J31.2 (SWDIO/TMS); also elsewhere on the board
VBUS: D1.4 (VDD), D2.4 (VDD), J30.A4 (VBUS), J30.A9 (VBUS), J30.B4 (VBUS), J30.B9 (VBUS); also elsewhere on the board
